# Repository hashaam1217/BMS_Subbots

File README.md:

# Battery Management System (BMS) for UBC Subbots

Custom 4-cell LiPo Battery Management System designed for the Subbots AUV.
Supports high-current discharge, full battery protection, and regulated power distribution for onboard electronics.

⸻

## Overview
	•	Designed for a 4S LiPo (Blue Robotics)
	•	Nominal: 14.8 V
	•	Max: 16.8 V
	•	Supports up to 80 A peak discharge
	•	Uses BQ76920 as the analog front end (AFE)
	•	Uses nRF54L15 as the microcontroller
	•	Generates regulated 12 V, 9 V, and 5 V rails using high-current buck regulators
	•	Low-side FET switching for discharge control
	•	Complete cell balancing, protection, and monitoring

⸻

### Battery Front End (BQ76920)
	•	Measures cell voltages (4S)
	•	Computes pack current using a Kelvin-routed shunt resistor
	•	Provides:
	•	Over-current (OCD) protection
	•	Short-circuit (SCD) protection
	•	Under-voltage and over-voltage protection
	•	Temperature monitoring (TS1)
	•	Cell balancing
	•	SRP/SRN routed as Kelvin sense lines with RC filtering
	•	PACK− and BAT− separated through the shunt resistor only

⸻

### Microcontroller (nRF54L15)
	•	Handles I²C communication with BQ76920
	•	ALERT pin used for interrupt-based event handling
	•	SWD interface exposed
	•	Powered from the regulated 3.3 V rail

⸻

## Power Regulation

### LM2596 (Pre-Regulator)
	•	Drops pack voltage down to ~5 V
	•	Used strictly to power the logic and control section of the AOZ2261NQI-11 regulators

### AOZ2261NQI-11 Buck Regulators
	•	Three independent outputs:
	•	12 V rail
	•	9 V rail
	•	5 V rail
	•	Each regulator includes:
	•	Separate AGND and PGND regions
	•	A single-point net tie back to PACK−
	•	Recommended output LC filtering
	•	Local decoupling at the VCC pin
	•	Designed to supply high peak currents needed by the AUV subsystems

⸻

## Grounding Strategy
	•	PACK− is the main high-current ground (GNDPWR)
	•	BAT− exists only for the shunt resistor and BQ76920 sense inputs
	•	AGND islands for analog and control circuits
	•	All grounds meet at a single point via net-tie:
	•	BAT− → shunt → PACK− → global ground reference
	•	Switching grounds (PGND) kept physically isolated from sensitive analog routing

⸻

## Connectors
	•	XT90 for main power input/output
	•	JST-XH for cell balance connector
	•	Multiple JST-XH headers for 12 V, 9 V, and 5 V outputs
	•	External thermistor header
	•	SWD programming header

⸻

## Protection and Sensing
	•	Low-value shunt resistor sized for 80 A peak thresholds
	•	OCD/SCD thresholds configured per BQ76920 limits
	•	RC network around SRP/SRN matches TI application notes
	•	Thermistor network matches BQ76920 TS1 recommendations
	•	Gate drive protection network included for discharge FET

⸻

### PCB Considerations
	•	LX nodes on AOZ regulators kept short and constrained
	•	Feedback resistors routed away from switching nets
	•	BQ76920 input filters placed as close as possible to pins
	•	Shunt resistor placed directly between PACK− and BAT− with symmetric Kelvin routing
	•	Output connectors isolated from analog area
	•	Power planes separated into:
	•	GNDPWR (high-current)
	•	GNDA (AFE, MCU, feedback)
	•	Tied at a single net-tie

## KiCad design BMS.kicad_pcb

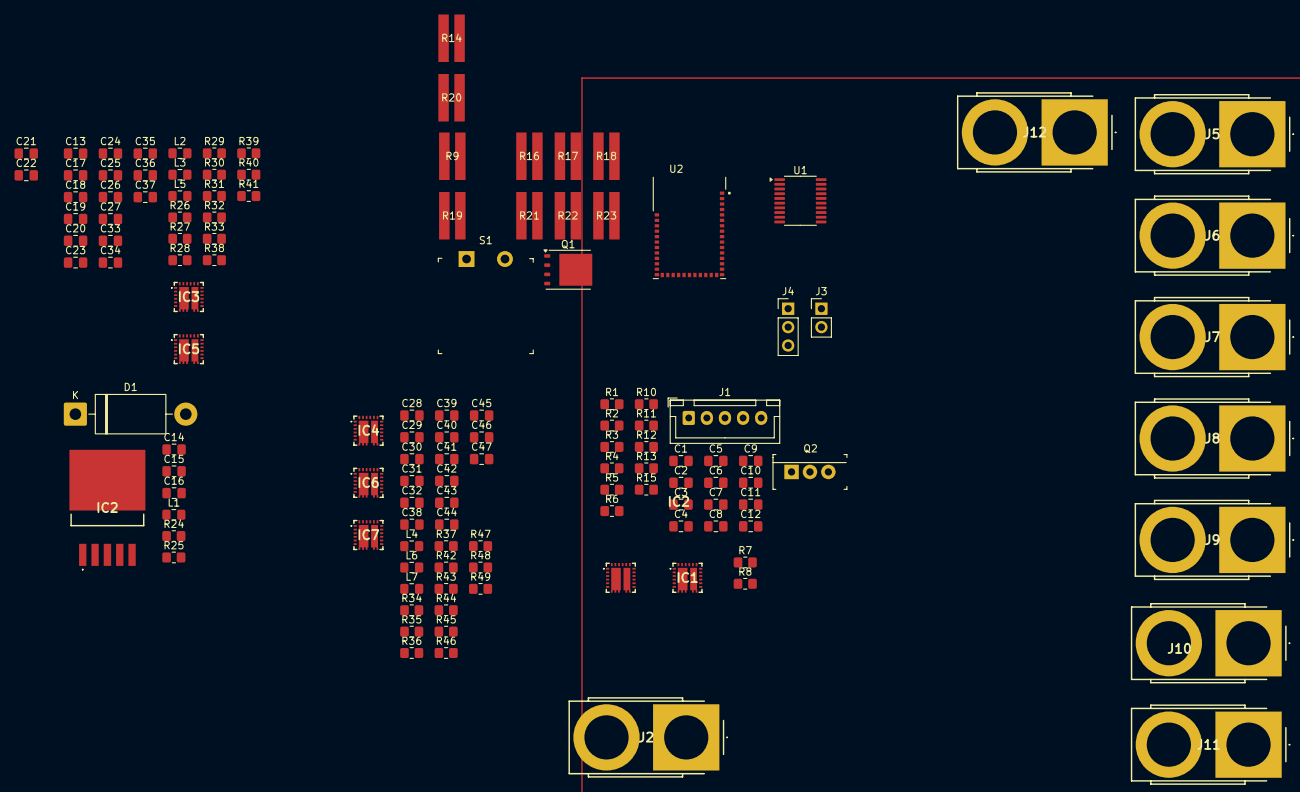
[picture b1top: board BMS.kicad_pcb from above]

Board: 2 copper layers, 129 parts (0 on the bottom side), 64 nets.

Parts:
C1, C2, C3, C4, C5, C6, C12: 1u; C_0805_2012Metric_Pad1.18x1.45mm_HandSolder
C7: 10u; C_0805_2012Metric_Pad1.18x1.45mm_HandSolder
C8, C9, C10, C19, C21, C24, C31, C32, C34, C38: 100n; C_0805_2012Metric_Pad1.18x1.45mm_HandSolder
C11, C17, C26, C36, C42, C43, C44: 4u7; C_0805_2012Metric_Pad1.18x1.45mm_HandSolder
C13, C16, C25, C35, C39, C40, C41: 10n; C_0805_2012Metric_Pad1.18x1.45mm_HandSolder
C14, C22: 100u; C_0805_2012Metric_Pad1.18x1.45mm_HandSolder
C15: 220u; C_0805_2012Metric_Pad1.18x1.45mm_HandSolder
C18, C20, C23, C27, C28, C29, C30, C33, C37, C45, C46, C47: 22u; C_0805_2012Metric_Pad1.18x1.45mm_HandSolder
D1: 1N5822; D_DO-201AD_P15.24mm_Horizontal
IC1, IC2, IC3, IC4, IC5, IC6, IC7: AOZ2261NQI-11; AOZ2261NQI11
IC2#2: LM2596DSADJG
J1: Conn_01x05_Pin; JST_XH_B5B-XH-A_1x05_P2.50mm_Vertical
J2, J5, J6, J7, J8, J9, J10, J11, J12: XT90PB-F; XT90PBF
J3: Conn_01x02_Pin; PinHeader_1x02_P2.54mm_Vertical
J4: Conn_01x03_Pin; PinHeader_1x03_P2.54mm_Vertical
L1: 33u; L_0805_2012Metric_Pad1.15x1.40mm_HandSolder
L2, L3, L4, L5, L6, L7: 1u; L_0805_2012Metric_Pad1.15x1.40mm_HandSolder
Q1: BSC028N06LS3; TDSON-8-1
Q2: IRLB3813PBF; TO-220-3
R1, R2, R3, R4, R5, R6, R11, R12: 100; R_0805_2012Metric_Pad1.20x1.40mm_HandSolder
R7: 4k7'; R_0805_2012Metric_Pad1.20x1.40mm_HandSolder
R8, R15: 4k7; R_0805_2012Metric_Pad1.20x1.40mm_HandSolder
R9, R14, R16, R17, R18, R19, R20, R21, R22, R23: 13m; RES_LTR100L_ROM
R10: 1M; R_0805_2012Metric_Pad1.20x1.40mm_HandSolder
R13, R29, R33, R41, R45, R47, R49: 10k; R_0805_2012Metric_Pad1.20x1.40mm_HandSolder
R24: 3k1; R_0805_2012Metric_Pad1.20x1.40mm_HandSolder
R25: 1k; R_0805_2012Metric_Pad1.20x1.40mm_HandSolder
R26, R27, R30, R31, R34, R35, R36, R37, R38, R39, R42, R43: 100k; R_0805_2012Metric_Pad1.20x1.40mm_HandSolder
R28, R44: 190k; R_0805_2012Metric_Pad1.20x1.40mm_HandSolder
R32, R46: 140k; R_0805_2012Metric_Pad1.20x1.40mm_HandSolder
R40, R48: 75k; R_0805_2012Metric_Pad1.20x1.40mm_HandSolder
S1: GPTS203211B; PushButton_12x12mm_THT_GPTS203211B
U1: BQ76920PW; TSSOP-20_4.4x6.5mm_P0.65mm
U2: 453-00001R; XCVR_453-00001R

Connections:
5VOUT: C37.1, C47.1, J11.2, J12.2, L5.2, L7.2, R40.2, R48.2
9VOUT: C27.1, C46.1, J9.2, J10.2, L3.2, L6.2, R32.2, R46.2
12VOUT: C20.1, C45.1, J7.2, J8.2, L2.2, L4.2, R28.2, R44.2
+5V: C15.1, C16.2, C17.1, C26.1, C36.1, C42.1, C43.1, C44.1, IC1.21 (VCC), IC3.21 (VCC), IC4.21 (VCC), IC5.21 (VCC), IC6.21 (VCC), IC7.21 (VCC), L1.2, R24.2, R26.1, R31.1, R37.1, R39.1, R42.1, R43.1
/ALERT: U1.20 (ALERT), U2.23 (P1.04/AIN0/CLK)
/EN5: IC5.2 (EN/DISCHG), IC7.2 (EN/DISCHG), U2.12 (P2.05)
/EN9: IC3.2 (EN/DISCHG), IC6.2 (EN/DISCHG), U2.38 (P2.06/CLK)
/EN12: IC1.2 (EN/DISCHG), IC4.2 (EN/DISCHG), U2.4 (P2.07)
/PGOOD5: IC5.1 (PGOOD), IC7.1 (PGOOD), R39.2, R43.2, U2.8 (P2.02)
/PGOOD9: IC3.1 (PGOOD), IC6.1 (PGOOD), R31.2, R42.2, U2.13 (P2.03)
/PGOOD12: IC1.1 (PGOOD), IC4.1 (PGOOD), R26.2, R37.2
/Power Distribution/FB5: IC5.5 (FB), IC7.5 (FB), R40.1, R41.2, R48.1, R49.2
/Power Distribution/FB9: IC3.5 (FB), IC6.5 (FB), R32.1, R33.2, R46.1, R47.2
/Power Distribution/FB12: IC1.5 (FB), IC4.5 (FB), R28.1, R29.2, R44.1, R45.2
/Power Distribution/LX5: C34.1, C38.1, IC5.10 (LX_1), IC5.11 (LX_2), IC5.16 (LX_3), IC5.17 (LX_4), IC5.18 (LX_5), IC5.25 (LX_6), IC7.10 (LX_1), IC7.11 (LX_2), IC7.16 (LX_3), IC7.17 (LX_4), IC7.18 (LX_5), IC7.25 (LX_6), L5.1, L7.1
/Power Distribution/LX9: C24.1, C32.1, IC3.10 (LX_1), IC3.11 (LX_2), IC3.16 (LX_3), IC3.17 (LX_4), IC3.18 (LX_5), IC3.25 (LX_6), IC6.10 (LX_1), IC6.11 (LX_2), IC6.16 (LX_3), IC6.17 (LX_4), IC6.18 (LX_5), IC6.25 (LX_6), L3.1, L6.1
/Power Distribution/LX12: C19.1, C31.1, IC1.10 (LX_1), IC1.11 (LX_2), IC1.16 (LX_3), IC1.17 (LX_4), IC1.18 (LX_5), IC1.25 (LX_6), IC4.10 (LX_1), IC4.11 (LX_2), IC4.16 (LX_3), IC4.17 (LX_4), IC4.18 (LX_5), IC4.25 (LX_6), L2.1, L4.1
/REGOUT: C11.1, R7.1, R8.1, U1.8 (REGOUT), U2.26 (VDD_NRF)
/RegulatorInput/Feedback: C16.1, IC2#2.4 (FEEDBACK), R24.1, R25.1
/RegulatorInput/Output: D1.1 (K), IC2#2.2 (OUTPUT), L1.1
/SCL0: R8.2, U1.5 (SCL), U2.14 (P1.03/NFC2/CLK)
/SDA0: R7.2, U1.4 (SDA), U2.15 (P1.02/NFC1)
/SRN: C9.1, C10.1, R12.1, U1.19 (SRN)
/SRP: C8.1, C10.2, R11.1, U1.18 (SRP)
/SWDIO: J4.1, U2.5 (SWDIO)
/TS1: J3.1, R13.2, R15.1, U1.6 (TS1)
/VC0: R5.1, U1.17 (VC0)
/VC1: R4.1, S1.1, U1.16 (VC1)
/VC2: R3.1, U1.15 (VC2)
/VC3: R2.1, U1.13 (VC4), U1.14 (VC3)
/VC4: R1.1, U1.12 (VC5)
GND1: C4.2, C5.1, C5.2, C6.2, C7.2, C8.2, C9.2, C11.2, C12.2, C21.2, C22.2, J1.1, J2.1, R5.2, R9.2, R11.2, R14.2, R16.2, R17.2, R18.2, R19.2, R20.2, R21.2, R22.2, R23.2, U1.3 (VSS)
GNDA: C13.2, C17.2, C25.2, C26.2, C35.2, C36.2, C39.2, C40.2, C41.2, C42.2, C43.2, C44.2, IC1.3 (MODE), IC1.4 (AGND), IC2.3 (MODE), IC3.3 (MODE), IC3.4 (AGND), IC4.3 (MODE), IC4.4 (AGND), IC5.3 (MODE), IC5.4 (AGND), IC6.3 (MODE), IC6.4 (AGND), IC7.3 (MODE), IC7.4 (AGND), R29.1, R33.1, R41.1, R45.1, R47.1, R49.1
GNDPWR: C18.2, C20.2, C23.2, C27.2, C28.2, C29.2, C30.2, C33.2, C37.2, C45.2, C46.2, C47.2, IC1.12 (PGND_1), IC1.13 (PGND_2), IC1.14 (PGND_3), IC1.15 (PGND_4), IC3.12 (PGND_1), IC3.13 (PGND_2), IC3.14 (PGND_3), IC3.15 (PGND_4), IC4.12 (PGND_1), IC4.13 (PGND_2), IC4.14 (PGND_3), IC4.15 (PGND_4), IC5.12 (PGND_1), IC5.13 (PGND_2), IC5.14 (PGND_3), IC5.15 (PGND_4), IC6.12 (PGND_1), IC6.13 (PGND_2), IC6.14 (PGND_3), IC6.15 (PGND_4), IC7.12 (PGND_1), IC7.13 (PGND_2), IC7.14 (PGND_3), IC7.15 (PGND_4)
unnamed: C19.2, IC1.20 (BST)
unnamed: C13.1, IC1.23 (SS)
unnamed: IC1.6 (TON), R27.1
unnamed: C24.2, IC3.20 (BST)
unnamed: C25.1, IC3.23 (SS)
unnamed: IC3.6 (TON), R30.1
unnamed: C31.2, IC4.20 (BST)
unnamed: C39.1, IC4.23 (SS)
unnamed: IC4.6 (TON), R34.1
unnamed: C34.2, IC5.20 (BST)
unnamed: C35.1, IC5.23 (SS)
unnamed: IC5.6 (TON), R38.1
unnamed: C32.2, IC6.20 (BST)
unnamed: C40.1, IC6.23 (SS)
unnamed: IC6.6 (TON), R35.1
unnamed: C38.2, IC7.20 (BST)
unnamed: C41.1, IC7.23 (SS)
unnamed: IC7.6 (TON), R36.1
unnamed: C3.2, C4.1, J1.2, R4.2
unnamed: C2.2, C3.1, J1.3, R3.2
unnamed: C1.2, C2.1, J1.4, R2.2
unnamed: C1.1, J1.5, R1.2
unnamed: Q1.1 (S), Q1.2 (S), Q1.3 (S)
unnamed: Q2.1 (G), R10.1, U1.1 (DSG)
unnamed: Q2.3 (S), R9.1, R10.2, R12.2, R14.1, R16.1, R17.1, R18.1, R19.1, R20.1, R21.1, R22.1, R23.1
unnamed: R13.1, S1.2
unnamed: C7.1, R6.2, U1.10 (BAT)
unnamed: C12.1, U1.7 (CAP1)
PACK+: C6.1, C14.1, C18.1, C21.1, C22.1, C23.1, C28.1, C29.1, C30.1, C33.1, IC1.7 (IN_1), IC1.8 (IN_2), IC1.9 (IN_3), IC1.22 (IN_4), IC1.24 (IN_5), IC2#2.1 (VIN), IC3.7 (IN_1), IC3.8 (IN_2), IC3.9 (IN_3), IC3.22 (IN_4), IC3.24 (IN_5), IC4.7 (IN_1), IC4.8 (IN_2), IC4.9 (IN_3), IC4.22 (IN_4), IC4.24 (IN_5), IC5.7 (IN_1), IC5.8 (IN_2), IC5.9 (IN_3), IC5.22 (IN_4), IC5.24 (IN_5), IC6.7 (IN_1), IC6.8 (IN_2), IC6.9 (IN_3), IC6.22 (IN_4), IC6.24 (IN_5), IC7.7 (IN_1), IC7.8 (IN_2), IC7.9 (IN_3), IC7.22 (IN_4), IC7.24 (IN_5), J2.2, J5.2, J6.2, R6.1, R27.2, R30.2, R34.2, R35.2, R36.2, R38.2, U1.9 (REGSRC)
PACK-: C14.2, C15.2, D1.2 (A), IC2#2.3 (GROUND_1), IC2#2.5 (~ON/OFF), IC2#2.6 (GROUND_2), J3.2, J4.3, J5.1, J6.1, J7.1, J8.1, J9.1, J10.1, J11.1, J12.1, Q1.5 (D), Q2.2 (D), R15.2, R25.2, U2.1 (GND), U2.16 (GND), U2.27 (GND), U2.39 (GND)

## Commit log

2025-11-28 Added Todo
